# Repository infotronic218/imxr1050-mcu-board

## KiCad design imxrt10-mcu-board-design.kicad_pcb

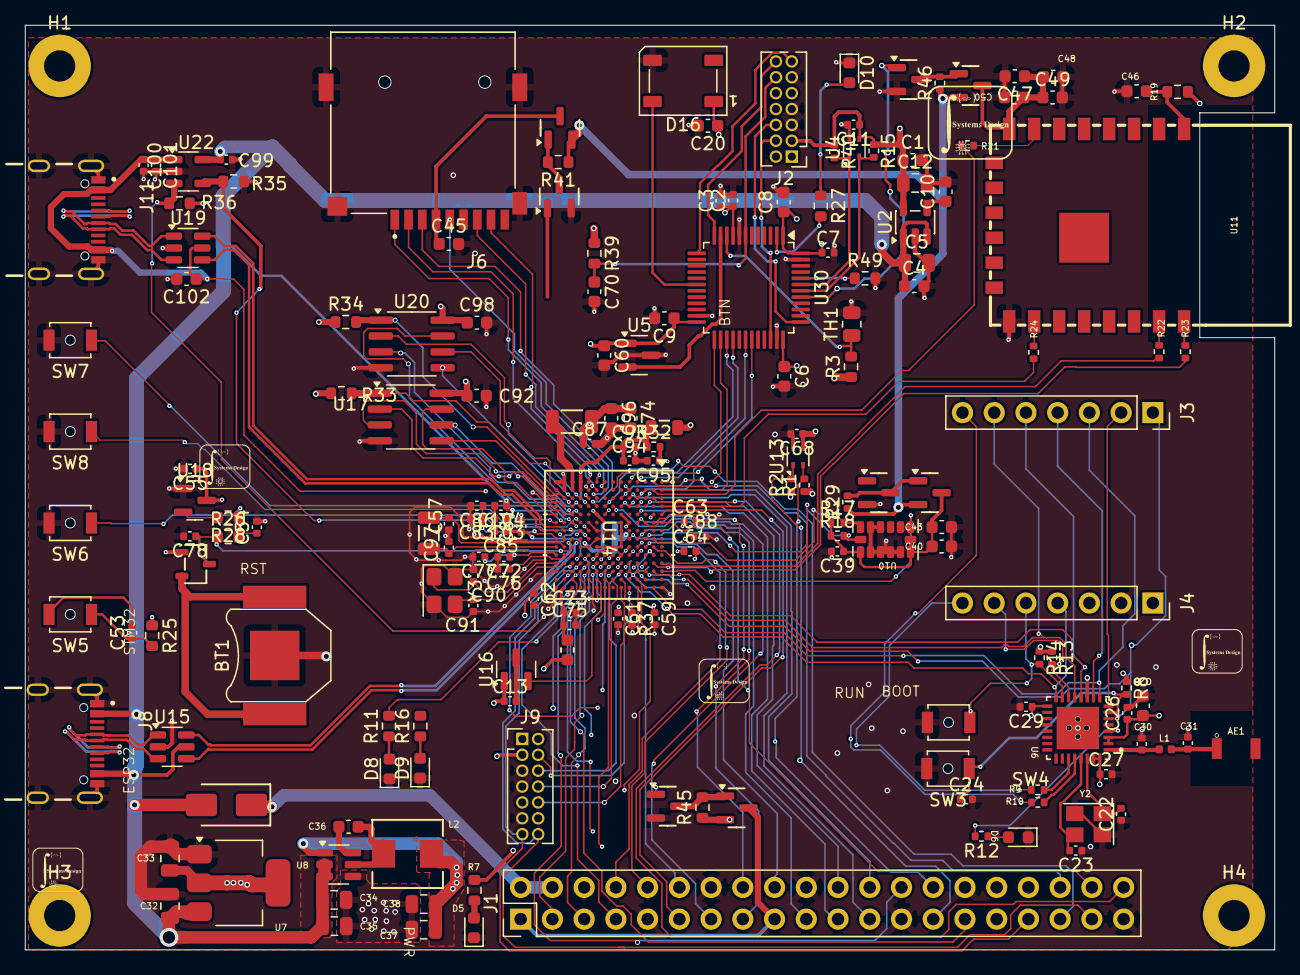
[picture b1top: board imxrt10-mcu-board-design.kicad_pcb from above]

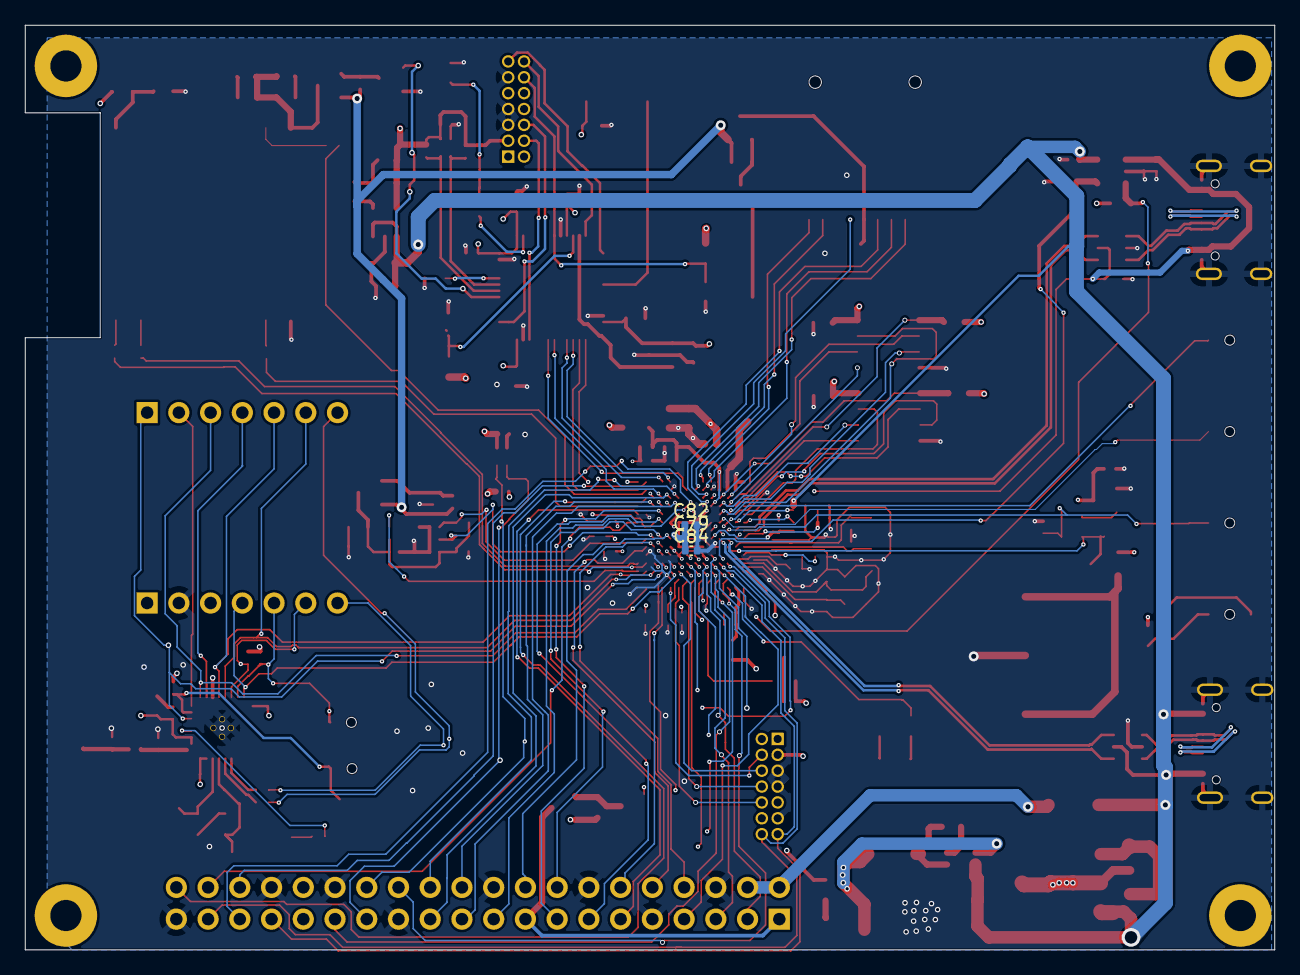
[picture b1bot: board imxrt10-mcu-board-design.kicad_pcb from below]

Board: 4 copper layers, 100.0 x 74.0 mm, 182 parts (3 on the bottom side), 158 nets.

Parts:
AE1: RFANT3216120A5T; FILTER-SMD_1206-2P-L3.2-W1.6-L
BT1: Battery_Cell; BatteryHolder_Keystone_2998_1x6.8mm
C1, C8, C9, C36, C40, C45, C46, C47, C60, C70, C92, C98: 100n; C_0603_1608Metric
C2, C3, C7, C73, C79, C93, C94, C99, C100: 2.2u; C_0402_1005Metric
C4, C10: 470n; C_0603_1608Metric
C5, C12: 10u; C_0805_2012Metric
C6, C28, C43, C48, C49, C50, C74, C96, C102: 10uF; C_0603_1608Metric
C11, C13, C24, C26, C27, C29, C53, C54, C55, C59, C61, C62, C63, C64, C68, C75, C82, C84, C87, C88, C101, C103, C104: 100n; C_0402_1005Metric
C20: 22u; C_0603_1608Metric
C22, C23, C57, C90, C91, C97: 10pF; C_0402_1005Metric
C30, C31: 1.5pF; C_0402_1005Metric
C32, C33, C34, C35, C37, C38: 22uF; C_0805_2012Metric
C39, C77, C85, C86: 10uF; C_0402_1005Metric
C72, C76, C78, C81, C83: 220n; C_0402_1005Metric
C95: 0.22u; C_0402_1005Metric
D5, D6, D8: LED, RED; LED_0603_1608Metric
D9: LED, White; LED_0603_1608Metric
D10: LED, Yellow; LED_0603_1608Metric
D12: BAV70-C68978; SOT-23-3_L3.0-W1.7-P0.95-LS2.9-BR
D13: SS34; D_SMA
D16: LED WS2812B; LED_WS2812B_PLCC4_5.0x5.0mm_P3.2mm
FB2: FB_0805
FB3: FB_0603
H1, H2, H3, H4: MountingHole_Pad; MountingHole_2.5mm_Pad
J1: Conn_02x20_Odd_Even; PinHeader_2x20_P2.54mm_Vertical
J2, J9: Conn_ST_STDC14; PinHeader_2x07_P1.27mm_Vertical
J3, J4: Conn_01x07; PinSocket_1x07_P2.54mm_Vertical
J6: MSD-4-A; CUI_MSD-4-A
J8, J11: USB4105-GF-A; GCT_USB4105-GF-A
L1: 2.4nH; L_0402_1005Metric
L2: 3.3uH; LMLP0506M3R3DTAS_AVX
L3: 4.7uH,25mA; L_1206
Q1, Q2, Q3, Q8: HL3401; Q_SOT-23
Q4, Q5, Q6, Q7: 2N7002K; Q_SOT-23
R1, R2, R8, R13, R14, R15, R17, R18, R29, R37, R40, R46: 10K; R_0402_1005Metric
R3, R19, R25, R33, R34, R35, R36, R39, R41, R45, R49: 10K; R_0603_1608Metric
R7, R11, R16, R27, R28: 750R; R_0603_1608Metric
R9: 0R; R_0402_1005Metric
R10: 470R; R_0402_1005Metric
R12: 750R; R_0402_1005Metric
R21, R22, R23, R24: 1K; R_0402_1005Metric
R26: 100K; R_0603_1608Metric
R32: 30K; R_0402_1005Metric
SW3, SW4, SW5, SW7, SW8: BOOT; SW_SPST_B3U-1000P-B
SW6: RST; SW_SPST_B3U-1000P-B
TH1: Thermistor_NTC 10k; R_0805_2012Metric
U2: SPX3819M5-L-3-3; SOT-23-5
U4, U13: SHT4x; Sensirion_DFN-4_1.5x1.5mm_P0.8mm_SHT4x_NoCentralPad
U5, U16: MCP9701T-E/TT; SOT-23
U6: ESP32-C3FH4
U7: AMS1117-3.3; SOT-223-3_TabPin2
U8: AP63203WU; TSOT-23-6
U10: ADXL343; LGA-14_3x5mm_P0.8mm_LayoutBorder1x6y
U11: WIZFI360-PA; WIFIM-SMD_WIZFI360-PA
U14: MIMXRT1052DVL6B; MAPBGA196_10X10_NXP
U15, U19: USBLC6-2SC6; SOT-23-6
U17: W25Q128JVS; SOIC-8_3.9x4.9mm_P1.27mm
U18: TPS3839DBZ; SOT-23
U20: APS1604M-3SQRx-SN; SOIC-8_3.9x4.9mm_P1.27mm
U22: TPS2051CDBV; SOT-23-5
U30: STM32F103C8Tx; LQFP-48_7x7mm_P0.5mm
X1: Q13FC1350000400; FC-135R_L3.2-W1.5
Y2, Y3: 40MHz, X252040MMB4SI; Crystal_SMD_3225-4Pin_3.2x2.5mm

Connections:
+3.3V: C13.1, C26.1, C27.1, C28.1, C29.1, C33.1, C55.1, C59.1, C61.1, C62.1, C63.1, C64.1, C68.1, C92.1, C98.1, D12.1, FB2.1, FB3.2, J9.3 (VCC), R1.1, R2.1, R7.2, R8.1, R13.1, R14.1, R19.1, R25.1, R33.1, R34.1, R36.1, U6.2 (VDD3P3), U6.3 (VDD3P3), U6.11 (VDD3P3_RTC), U6.17 (VDD3P3_CPU), U6.31 (VDDA), U6.32 (VDDA), U7.2 (VO), U13.3 (VDD), U14.E6 (NVCC_EMC), U14.E9 (NVCC_GPIO), U14.F5 (NVCC_EMC), U14.F10 (NVCC_GPIO), U14.J10 (NVCC_GPIO), U14.P12 (VDD_HIGH_IN), U16.1 (Vdd), U17.8 (VCC), U18.3 (VDD), U20.8 (VDD)
+3.3V1: C1.1, C2.1, C3.1, C6.1, C7.1, C8.1, C9.1, C11.1, C12.1, C20.1, C60.1, D16.1 (VDD), J2.3 (VCC), R3.1, R15.1, R39.1, R40.1, U2.5 (OUT), U4.3 (VDD), U5.1 (Vdd), U30.1 (VBAT), U30.9 (VDDA), U30.24 (VDD), U30.36 (VDD), U30.48 (VDD)
+3.3V_EXT: J1.1, J1.17, Q2.3 (D)
+3.3V_MPU: C39.1, C40.1, C43.1, Q8.3 (D), R17.1, R18.1, U10.1 (Vdd_I/O), U10.6 (Vs), U10.7 (~CS)
+3.3V_SD: C45.1, J6.4 (VDD), Q1.3 (D)
+3.3V_SYS: C37.1, C38.1, L2.2, Q1.2 (S), Q2.2 (S), Q3.2 (S), Q8.2 (S), R29.1, R41.1, R45.1, R46.1, U8.1 (FB)
+3.3V_WIFI: C47.1, C48.1, C49.1, C50.1, Q3.3 (D), U11.8 (VCC)
/EXT_IO0_I2C0_SCL: J1.28, R1.2, U13.2 (SCL), U14.J11 (GPIO_AD_B1_00)
/EXT_IO1_I2C0_SDA: J1.27, R2.2, U13.1 (SDA), U14.K11 (GPIO_AD_B1_01)
/EXT_IO2_I2C1_SDA: J1.3, U14.J12 (GPIO_AD_B1_06)
/EXT_IO3_I2C1_SCL: J1.5, U14.K10 (GPIO_AD_B1_07)
/EXT_IO4: J1.7, U14.L12 (GPIO_AD_B1_04)
/EXT_IO5: J1.29, U14.K12 (GPIO_AD_B1_05)
/EXT_IO6: J1.31, U14.H13 (GPIO_AD_B1_08)
/EXT_IO7: J1.26, U14.M13 (GPIO_AD_B1_09)
/EXT_IO8_SPI_CS: J1.24, U14.F3 (GPIO_EMC_01)
/EXT_IO9_SPI_MISO: J1.21, U14.F4 (GPIO_EMC_02)
/EXT_IO10_SPI_MOSI: J1.19, U14.G4 (GPIO_EMC_03)
/EXT_IO11_SPI_SCK: J1.23, U14.E3 (GPIO_EMC_00)
/EXT_IO12: J1.32, U14.L13 (GPIO_AD_B1_10)
/EXT_IO13_UART2_TX: J1.33, J9.13 (VCP_RX), U14.M12 (GPIO_AD_B1_03)
/EXT_IO14_UART1_RX: J1.8, U14.C9 (GPIO_B0_09)
/EXT_IO15_UART1_TX: J1.10, U14.B9 (GPIO_B0_08)
/EXT_IO16_UART1_RTS: J1.36, U14.B1 (GPIO_EMC_15)
/EXT_IO17_UART1_CTS: J1.11, U14.A5 (GPIO_EMC_16)
/EXT_IO18: J1.12, U14.D14 (GPIO_B1_13)
/EXT_IO19: J1.35, U14.H4 (GPIO_EMC_07)
/EXT_IO20: J1.38, U14.A6 (GPIO_EMC_13)
/EXT_IO21: J1.40, U14.B3 (GPIO_EMC_26)
/EXT_IO22: J1.15, U14.D5 (GPIO_EMC_32)
/EXT_IO23_CAN_TX: J1.16, U14.D8 (GPIO_B0_03)
/EXT_IO24_CAN_RX: J1.18, U14.E8 (GPIO_B0_02)
/EXT_IO25: J1.22, U14.C4 (GPIO_EMC_33)
/EXT_IO26_UART2_RX: J1.37, J9.14 (VCP_TX), U14.L11 (GPIO_AD_B1_02)
/EXT_IO27: J1.13, U14.D6 (GPIO_EMC_38)
/EXT_PWR_EN: Q6.1 (G), U14.D13 (GPIO_B1_12)
/MPU_INT: U10.8 (INT1), U14.A12 (GPIO_B1_08)
/USART3_CTS: R24.2, U14.A4 (GPIO_EMC_17)
/USART3_RTS: R21.2, U14.B2 (GPIO_EMC_18)
/USART3_RX: R23.2, U14.B11 (GPIO_B1_01)
/USART3_TX: R22.2, U14.A11 (GPIO_B1_00)
/WIZ_PWEN: Q5.1 (G), U30.41 (PB5)
/WIZ_RST: C46.1, R19.2, U11.1 (RST)
/esp32_wifi_section/ESP_RX: J4.7, R9.1, U14.M11 (GPIO_AD_B0_02)
/esp32_wifi_section/ESP_STATUS_LED: R12.2, U6.4 (XTAL_32K_P)
/esp32_wifi_section/ESP_TX: J3.7, R10.1, U14.G11 (GPIO_AD_B0_03)
/esp32_wifi_section/IO2_SPI_MISO: J3.1, U6.6 (GPIO2), U14.D12 (GPIO_B1_05)
/esp32_wifi_section/IO3_HS: J3.2, U6.8 (GPIO3)
/esp32_wifi_section/IO4_DATA_RDY: J3.3, U6.9 (MTMS), U14.B14 (GPIO_B1_15)
/esp32_wifi_section/IO5: J3.4, U6.10 (MTDI)
/esp32_wifi_section/IO6_SPI_CLK: J3.5, U6.12 (MTCK), U14.B12 (GPIO_B1_07)
/esp32_wifi_section/IO7_SPI_MOSI: J3.6, U6.13 (MTDO), U14.C12 (GPIO_B1_06)
/esp32_wifi_section/IO8: J4.6, R13.2, U6.14 (GPIO8)
/esp32_wifi_section/IO9: J4.5, R14.2, SW4.1, U6.15 (GPIO9)
/esp32_wifi_section/IO10_CS: J4.4, U6.16 (GPIO10), U14.E12 (GPIO_B1_04)
/esp32_wifi_section/LNA_IN: C30.1, L1.1, U6.1 (LNA_IN)
/esp32_wifi_section/RST: C24.1, R8.2, SW3.1, U6.7 (CHIP_EN)
/esp32_wifi_section/XTAL_N: C23.2, U6.29 (XTAL_N), Y2.3
/esp32_wifi_section/XTAL_P: C22.2, U6.30 (XTAL_P), Y2.1
/imxrt10-schematic/ADC_IN0: U14.J13 (GPIO_AD_B1_11), U16.2 (Vout)
/imxrt10-schematic/D2+: J11.A6 (DP1), J11.B6 (DP2), U19.3 (I/O2)
/imxrt10-schematic/D2-: J11.A7 (DN1), J11.B7 (DN2), U19.1 (I/O1)
/imxrt10-schematic/D+: J8.A6 (DP1), J8.B6 (DP2), U15.3 (I/O2)
/imxrt10-schematic/D-: J8.A7 (DN1), J8.B7 (DN2), U15.1 (I/O1)
/imxrt10-schematic/I2C2_SCL: R18.2, U10.14 (SCL/SCLK), U14.C8 (GPIO_B0_04)
/imxrt10-schematic/I2C2_SDA: R17.2, U10.13 (SDA/SDI/SDIO), U14.B8 (GPIO_B0_05)
/imxrt10-schematic/JTAG_MODE: R37.1, U14.F13 (GPIO_AD_B0_08)
/imxrt10-schematic/JTAG_SWDCLK: J9.6 (JCLK/SWCLK), U14.F12 (GPIO_AD_B0_07)
/imxrt10-schematic/JTAG_SWDIO: J9.4 (JTMS/SWDIO), U14.E14 (GPIO_AD_B0_06)
/imxrt10-schematic/JTAG_TDI: J9.10 (JTDI/NC), U14.F14 (GPIO_AD_B0_09)
/imxrt10-schematic/JTAG_TDO: J9.8 (JTDO/SWO), U14.G13 (GPIO_AD_B0_10)
/imxrt10-schematic/LED1: R11.2, U14.M14 (GPIO_AD_B0_00)
/imxrt10-schematic/POR_B: C54.1, R26.2, R28.1, SW6.1, U14.M7 (POR_B)
/imxrt10-schematic/SPI1_CS0: U14.C6 (GPIO_EMC_30), U30.25 (PB12)
/imxrt10-schematic/SPI1_SCK: U14.A2 (GPIO_EMC_27), U30.26 (PB13)
/imxrt10-schematic/SPI1_SDI: U14.E1 (GPIO_EMC_29), U30.27 (PB14)
/imxrt10-schematic/SPI1_SDO: U14.D1 (GPIO_EMC_28), U30.28 (PB15)
/imxrt10-schematic/UART5_RX: U14.D3 (GPIO_EMC_24), U30.30 (PA9)
/imxrt10-schematic/UART5_TX: U14.G2 (GPIO_EMC_23), U30.31 (PA10)
/imxrt10-schematic/USB_HOST_PWR_EN: R35.1, U14.L10 (GPIO_AD_B0_15), U22.4 (EN)
/imxrt10-schematic/USB_HOST_PWR_OC: R36.2, U14.H14 (GPIO_AD_B0_14), U22.3 (~FLT)
/imxrt10-schematic/USB_OTG_1_D+: U14.L8 (USB_OTG1_DP), U15.4 (I/O2)
/imxrt10-schematic/USB_OTG_1_D-: U14.M8 (USB_OTG1_DN), U15.6 (I/O1)
/imxrt10-schematic/USB_OTG_2_D+: U14.P7 (USB_OTG2_DP), U19.4 (I/O2)
/imxrt10-schematic/USB_OTG_2_D-: U14.N7 (USB_OTG2_DN), U19.6 (I/O1)
/imxrt10-schematic/USR_BTN: C53.1, R25.2, SW5.1
/imxrt10-schematic/VDD_SNVS_IN: C78.1, D12.3, R26.1, U14.M9 (VDD_SNVS_IN)
/imxrt10-schematic/XTAL_N: C91.2, U14.N11 (XTALO), Y3.3
/imxrt10-schematic/XTAL_P: C90.2, U14.P11 (XTALI), Y3.1
/stm32f103-mcu-interface/BOOT0: R49.1, U30.44 (BOOT0)
/stm32f103-mcu-interface/DIN: D16.4 (DIN), U30.18 (PB0)
/stm32f103-mcu-interface/I2C1_SCL: R15.2, U4.2 (SCL), U30.42 (PB6)
/stm32f103-mcu-interface/I2C1_SDA: R40.2, U4.1 (SDA), U30.43 (PB7)
/stm32f103-mcu-interface/LED3: R27.2, U30.2 (PC13)
/stm32f103-mcu-interface/NRST: C70.1, J2.12 (~RST), R39.2, U30.7 (NRST)
/stm32f103-mcu-interface/NTC_TEMP: R3.2, TH1.1, U30.10 (PA0)
/stm32f103-mcu-interface/SWCLK: J2.6 (JCLK/SWCLK), U30.37 (PA14)
/stm32f103-mcu-interface/SWDIO: J2.4 (JTMS/SWDIO), U30.34 (PA13)
/stm32f103-mcu-interface/TH_Sensor: U5.2 (Vout), U30.11 (PA1)
/stm32f103-mcu-interface/UART2_RX: J2.13 (VCP_RX), U30.13 (PA3)
/stm32f103-mcu-interface/UART2_TX: J2.14 (VCP_TX), U30.12 (PA2)
FLEXSPI_A_CLK: U14.L4 (GPIO_SD_B1_07), U17.6 (CLK)
FLEXSPI_A_SD0: U14.P3 (GPIO_SD_B1_08), U17.5 (DI(IO0))
FLEXSPI_A_SD1: U14.N4 (GPIO_SD_B1_09), U17.2 (DO(IO1))
FLEXSPI_A_SD2: U14.P4 (GPIO_SD_B1_10), U17.3 (IO2)
FLEXSPI_A_SD3: U14.P5 (GPIO_SD_B1_11), U17.7 (IO3)
FLEXSPI_A_SS: R33.2, U14.L3 (GPIO_SD_B1_06), U17.1 (~CS)
FLEXSPI_B_CLK: U14.P2 (GPIO_SD_B1_04), U20.6 (SCLK)
FLEXSPI_B_SD0: U14.M4 (GPIO_SD_B1_03), U20.5 (SI/SIO0)
FLEXSPI_B_SD1: U14.M3 (GPIO_SD_B1_02), U20.2 (SO/SIO1)
FLEXSPI_B_SD2: U14.M5 (GPIO_SD_B1_01), U20.3 (SIO2)
FLEXSPI_B_SD3: U14.L5 (GPIO_SD_B1_00), U20.7 (SIO3)
FLEXSPI_B_SS: R34.2, U14.N3 (GPIO_SD_B1_05), U20.1 (~CE)
GND: BT1.2 (-), C1.2, C2.2, C3.2, C4.2, C5.2, C6.2, C7.2, C8.2, C9.2, C10.2, C11.2, C12.2, C13.2, C20.2, C22.1, C23.1, C24.2, C26.2, C27.2, C28.2, C29.2, C30.2, C31.2, C32.2, C33.2, C34.2, C35.2, C37.2, C38.2, C39.2, C40.2, C43.2, C45.2, C46.2, C47.2, C48.2, C49.2, C50.2, C54.2, C55.2, C57.1, C59.2, C60.2, C61.2, C62.2, C63.2, C64.2, C68.2, C70.2, C72.2, C73.2, C74.2, C75.2, C76.2, C77.2, C78.2, C79.2, C81.2, C82.2, C83.2, C84.2, C85.2, C86.2, C87.2, C88.2, C90.1, C91.1, C92.2, C93.2, C94.2, C95.2, C96.2, C97.1, C98.2, C99.2, C100.2, C101.2, C102.2, C103.2, C104.2, D5.1 (K), D6.1 (K), D8.1 (K), D9.1 (K), D10.1 (K), D16.3 (VSS), J1.6, J1.9, J1.14, J1.20, J1.25, J1.30, J1.34, J1.39, J2.5 (GND), J2.7 (GND), J2.11 (GNDDetect), J4.2, J6.6 (VSS), J6.G1 (COVER_GND), J6.G2 (COVER_GND), J6.G3 (COVER_GND), J6.G4 (COVER_GND), J8.A1_B12 (GND), J8.B1_A12 (GND), J8.SH1 (SHELL_GND), J8.SH2 (SHELL_GND), J8.SH3 (SHELL_GND), J8.SH4 (SHELL_GND), J9.5 (GND), J9.7 (GND), J9.11 (GNDDetect), J11.A1_B12 (GND), J11.B1_A12 (GND), J11.SH1 (SHELL_GND), J11.SH2 (SHELL_GND), J11.SH3 (SHELL_GND), J11.SH4 (SHELL_GND), Q4.2 (S), Q5.2 (S), Q6.2 (S), Q7.2 (S), R35.2, R37.2, R49.2, SW3.2, SW4.2, SW6.2, SW7.2, SW8.2, TH1.2, U2.2 (GND), U4.4 (VSS), U5.3 (GND), U6.33 (GND), U7.1 (GND), U8.4 (GND), U10.2 (GND), U10.3 (RES), U10.4 (GND), U10.5 (GND), U10.11 (RES), U10.12 (SDO/ADDR), U11.15 (GND), U13.4 (VSS), U14.A1 (VSS), U14.A14 (VSS), U14.B5 (VSS), U14.B10 (VSS), U14.E2 (VSS), U14.E13 (VSS), U14.G7 (VSS), U14.G8 (VSS), U14.H7 (VSS), U14.H8 (VSS), U14.J7 (VSS), U14.J8 (VSS), U14.K2 (VSS), U14.K6 (TEST_MODE), U14.K9 (NGND_KEL0), U14.K13 (VSS), U14.L9 (VSS), U14.N1 (DCDC_GND), U14.N2 (DCDC_GND), U14.N5 (VSS), U14.N8 (VSS), U14.P1 (VSS), U14.P14 (VSS), U15.2 (GND), U16.3 (GND), U17.4 (GND), U18.1 (GND), U19.2 (GND), U20.4 (VSS), U22.2 (GND), U30.8 (VSSA), U30.23 (VSS), U30.35 (VSS), U30.47 (VSS), Y2.2, Y2.4, Y3.2, Y3.4
unnamed: AE1.1 (A), C31.1, L1.2
unnamed: C53.2, SW5.2
unnamed: D5.2 (A), R7.1
unnamed: D6.2 (A), R12.1
unnamed: D8.2 (A), R11.1
unnamed: D9.2 (A), R16.1
unnamed: D10.2 (A), R27.1
unnamed: D13.1, J1.2, J1.4
unnamed: L3.1, U14.M1 (DCDC_LP), U14.M2 (DCDC_LP)
unnamed: Q1.1 (G), Q4.3 (D), R41.2
unnamed: Q2.1 (G), Q6.3 (D), R45.2
unnamed: Q3.1 (G), Q5.3 (D), R46.2
unnamed: Q7.3 (D), Q8.1 (G), R29.2
unnamed: C10.1, U2.4 (BP)
unnamed: R9.2, U6.27 (U0RXD)
unnamed: R10.2, U6.28 (U0TXD)
unnamed: C36.1, U8.6 (BST)
unnamed: C36.2, L2.1, U8.5 (SW)
unnamed: R21.1, U11.7 (PB9/CTS1)
unnamed: R24.1, U11.16 (PB10/RTSI)
unnamed: R22.1, U11.21 (RXD1/IIC_SCL)
unnamed: R23.1, U11.22 (TXD1/IIC_SDA)
unnamed: SW7.1, U14.M6 (ONOFF)
unnamed: C57.2, U14.N9 (RTC_XTALI), X1.1
unnamed: C97.2, U14.P9 (RTC_XTALO), X1.2
unnamed: SW8.1, U14.L6 (WAKEUP)
unnamed: C72.1, C77.1, U14.P10 (NVCC_PLL)
unnamed: C73.1, C75.1, FB3.1, U14.N14 (VDDA_ADC_3P3)
unnamed: C83.1, C86.1, U14.P8 (VDD_HIGH_CAP)
unnamed: C76.1, U14.M10 (VDD_SNVS_CAP)
unnamed: C81.1, C85.1, U14.K8 (VDD_USB_CAP)
unnamed: C93.1, C94.1, FB2.2, R32.1, U14.K4 (DCDC_IN_Q), U14.L1 (DCDC_IN), U14.L2 (DCDC_IN)
unnamed: C95.1, R32.2, U14.K3 (DCDC_PSWITCH)
unnamed: R28.2, U18.2 (~RESET)
SD_CMD: J6.3 (CMD), U14.J4 (GPIO_SD_B0_00)
SD_D0: J6.7 (DAT0), U14.J1 (GPIO_SD_B0_02)
SD_D1: J6.8 (DAT1), U14.K1 (GPIO_SD_B0_03)
SD_D2: J6.1 (DAT2), U14.H2 (GPIO_SD_B0_04)
SD_D3: J6.2 (CD/DAT3), U14.J2 (GPIO_SD_B0_05)
SD_SCK: J6.5 (CLK), U14.J3 (GPIO_SD_B0_01)
VBAT: BT1.1 (+), D12.2
VBUS: C4.1, C5.1, C32.1, C34.1, C35.1, C99.1, C104.1, D13.2, J8.A4_B9 (VBUS), J8.B4_A9 (VBUS), U2.1 (IN), U2.3 (EN), U7.3 (VI), U8.2 (EN), U8.3 (IN), U14.N6 (USB_OTG1_VBUS), U15.5 (VBUS), U22.5 (IN)
VBUS_HOST: C100.1, C101.1, C102.1, C103.1, J11.A4_B9 (VBUS), J11.B4_A9 (VBUS), U14.P6 (USB_OTG2_VBUS), U19.5 (VBUS), U22.1 (OUT)
VDD_CORE: C74.1, C79.1, C82.1, C84.1, C87.1, C88.1, C96.1, L3.2, U14.F6 (VDD_SOC_IN), U14.F7 (VDD_SOC_IN), U14.F8 (VDD_SOC_IN), U14.F9 (VDD_SOC_IN), U14.G6 (VDD_SOC_IN), U14.G9 (VDD_SOC_IN), U14.H6 (VDD_SOC_IN), U14.H9 (VDD_SOC_IN), U14.J5 (DCDC_SENSE), U14.J9 (VDD_SOC_IN)

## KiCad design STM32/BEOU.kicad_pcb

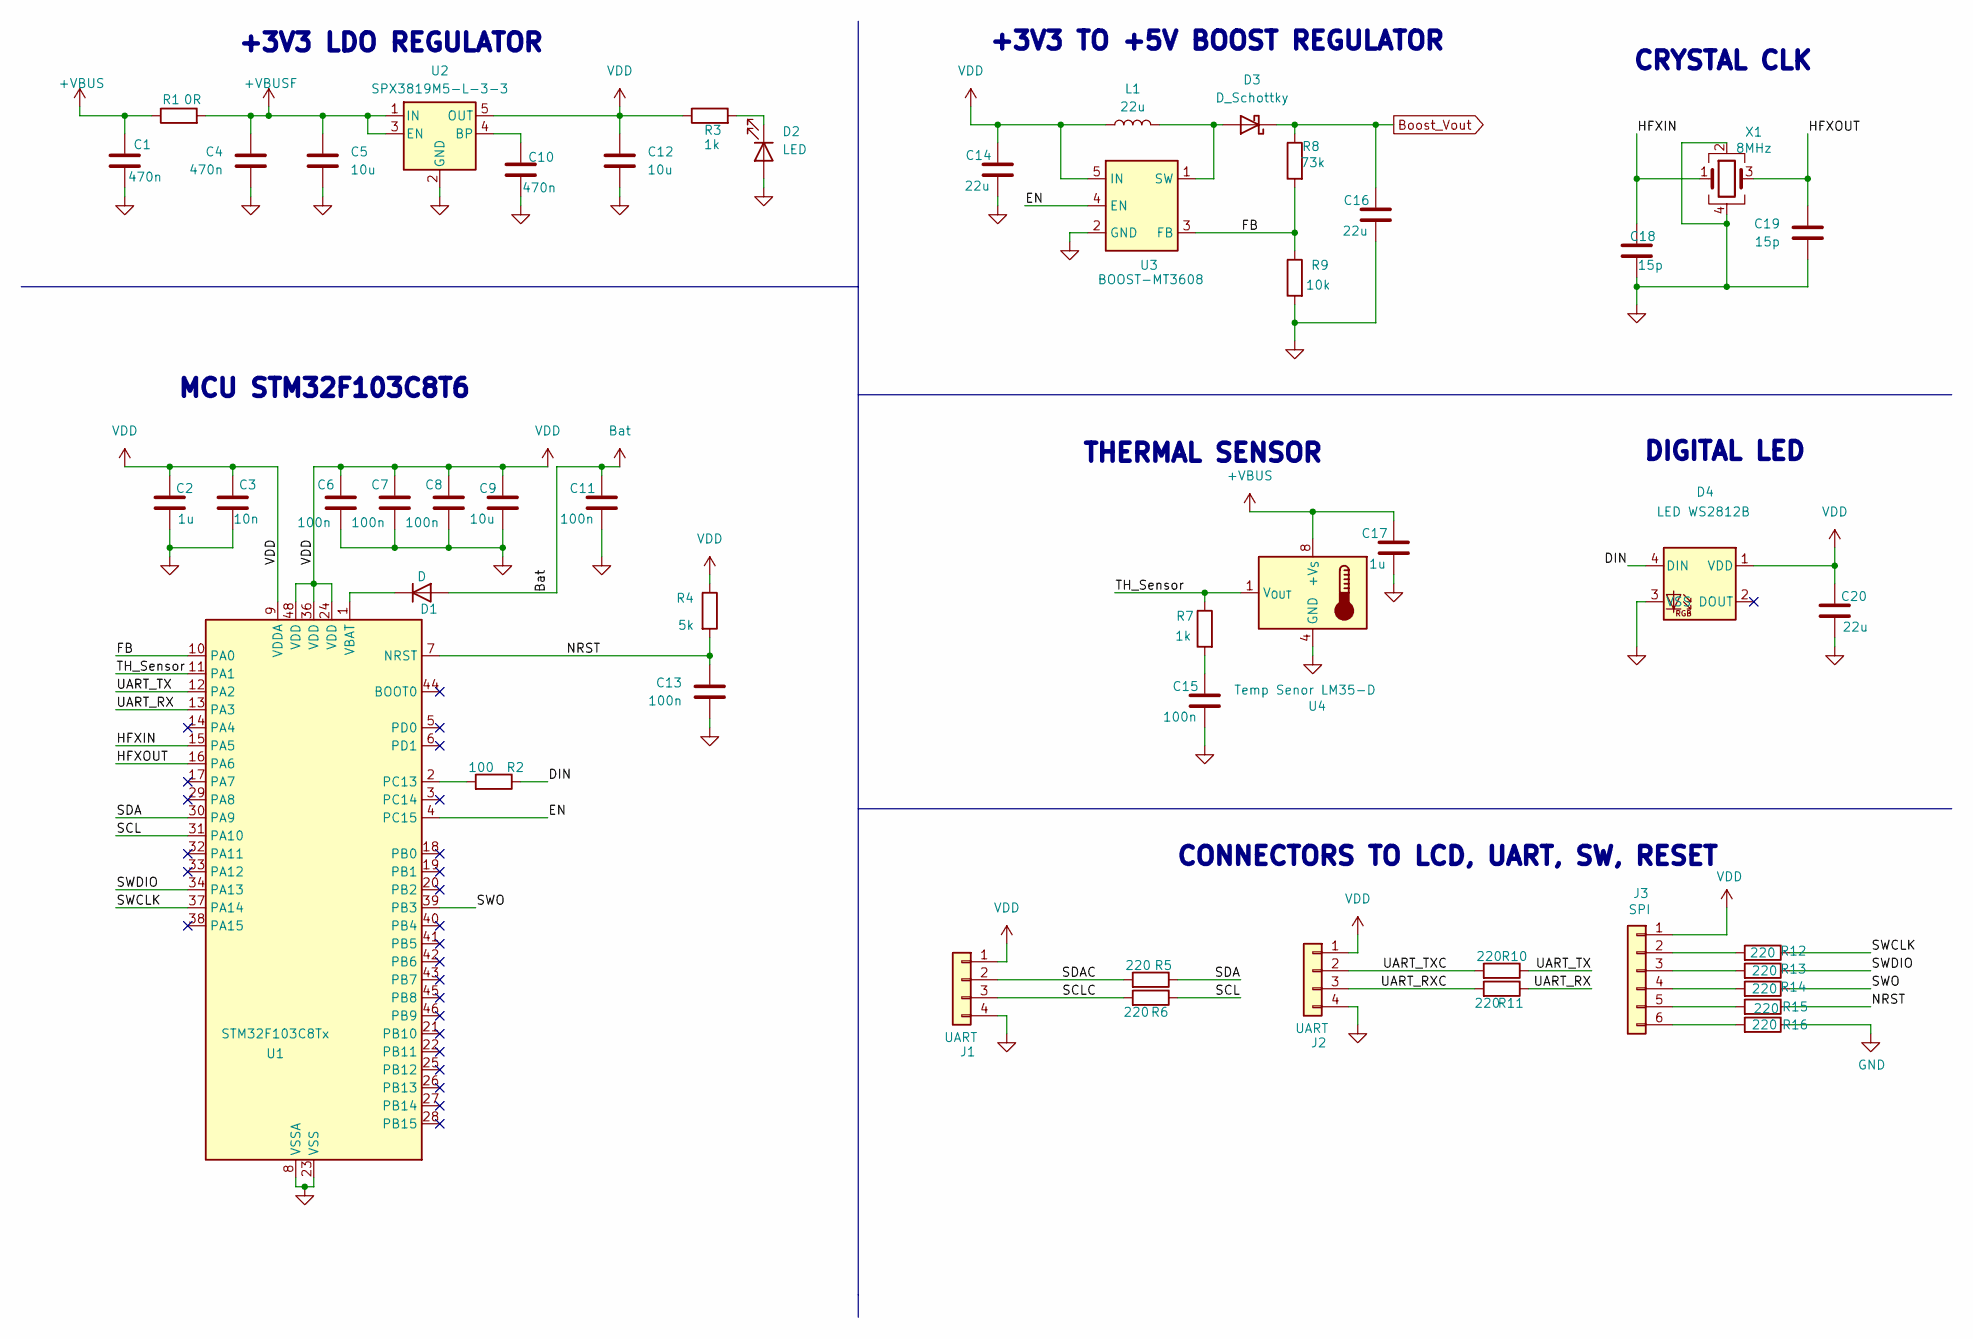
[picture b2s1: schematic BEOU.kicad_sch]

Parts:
C1, C4, C10: 470n; C_0603_1608Metric
C2, C17: 1u; C_0603_1608Metric
C3: 10n; C_0603_1608Metric
C5, C12: 10u; C_0805_2012Metric
C6, C7, C8, C11, C13, C15: 100n; C_0603_1608Metric
C9: 10u; C_0603_1608Metric
C14, C16, C20: 22u; C_0603_1608Metric
C18, C19: 15p; C_0603_1608Metric
D1: D; D_0201_0603Metric
D2: LED; LED_0603_1608Metric
D3: D_Schottky; D_0201_0603Metric
D4: LED WS2812B; LED_WS2812B_PLCC4_5.0x5.0mm_P3.2mm
J1, J2: UART; PinHeader_1x04_P2.54mm_Vertical
J3: SPI; JST_EH_B6B-EH-A_1x06_P2.50mm_Vertical
L1: 22u; L_0603_1608Metric
R1: 0R; R_0603_1608Metric
R2: 100; R_0201_0603Metric
R3: 1k; R_0603_1608Metric
R4: 5k; R_0603_1608Metric
R5, R6, R10, R11, R12, R13, R14, R15, R16: 220; R_0201_0603Metric
R7: 1k; R_0201_0603Metric
R8: 73k; R_0201_0603Metric
R9: 10k; R_0201_0603Metric
U1: STM32F103C8Tx; LQFP-48_7x7mm_P0.5mm
U2: SPX3819M5-L-3-3; SOT-23-5
U3: BOOST-MT3608; SOT-23-6
U4: Temp Senor LM35-D; SOIC-8_3.9x4.9mm_P1.27mm
X1: 8MHz; Crystal_SMD_3225-4Pin_3.2x2.5mm

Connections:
+VBUS: C1.1, C17.1, R1.1, U4.8 (+V_{S})
+VBUSF: C4.1, C5.1, R1.2, U2.1 (IN), U2.3 (EN)
/<NO NET>: C19.1, U1.16 (PA6), X1.3
/DIN: D4.4 (DIN), R2.1
/EN: U1.4 (PC15), U3.4 (EN)
/FB: R8.2, R9.1, U1.10 (PA0), U3.3 (FB)
/HFXIN: C18.1, U1.15 (PA5), X1.1
/NRST: C13.1, R4.2, R15.1, U1.7 (NRST)
/SCL: R6.1, U1.31 (PA10)
/SCLC: J1.3, R6.2
/SDA: R5.1, U1.30 (PA9)
/SDAC: J1.2, R5.2
/SWCLK: R12.1, U1.37 (PA14)
/SWDIO: R13.1, U1.34 (PA13)
/SWO: R14.1, U1.39 (PB3)
/TH_Sensor: R7.1, U1.11 (PA1), U4.1 (V_{OUT})
/UART_RX: R11.1, U1.13 (PA3)
/UART_RXC: J2.3, R11.2
/UART_TX: R10.1, U1.12 (PA2)
/UART_TXC: J2.2, R10.2
Bat: C11.1, D1.2 (A)
Boost_Vout: C16.1, D3.1 (K), R8.1
GND: C1.2, C2.2, C3.2, C4.2, C5.2, C6.2, C7.2, C8.2, C9.2, C10.2, C11.2, C12.2, C13.2, C14.2, C15.2, C16.2, C17.2, C18.2, C19.2, C20.2, D2.2 (A), D4.3 (VSS), J1.4, J2.4, R9.2, R16.1, U1.8 (VSSA), U1.23 (VSS), U1.35 (VSS), U1.47 (VSS), U2.2 (GND), U3.2 (GND), U4.4 (GND), X1.2, X1.4
unnamed: C15.1, R7.2
unnamed: D1.1 (K), U1.1 (VBAT)
unnamed: D2.1 (K), R3.2
unnamed: D3.2 (A), L1.2, U3.1 (SW)
unnamed: J3.2, R12.2
unnamed: J3.3, R13.2
unnamed: J3.4, R14.2
unnamed: J3.5, R15.2
unnamed: J3.6, R16.2
unnamed: R2.2, U1.2 (PC13)
unnamed: C10.1, U2.4 (BP)
VDD: C2.1, C3.1, C6.1, C7.1, C8.1, C9.1, C12.1, C14.1, C20.1, D4.1 (VDD), J1.1, J2.1, J3.1, L1.1, R3.1, R4.1, U1.9 (VDDA), U1.24 (VDD), U1.36 (VDD), U1.48 (VDD), U2.5 (OUT), U3.5 (IN)

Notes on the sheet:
DIGITAL LED
CRYSTAL CLK
THERMAL SENSOR
MCU STM32F103C8T6
+3V3 LDO REGULATOR
CONNECTORS TO LCD, UART, SW, RESET
+3V3 TO +5V BOOST REGULATOR

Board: 2 copper layers, 49 parts (0 on the bottom side), 35 nets, no tracks yet.

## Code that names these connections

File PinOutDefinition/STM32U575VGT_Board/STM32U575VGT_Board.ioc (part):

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Mcu.Name=STM32U575VGTx
Mcu.Package=LQFP100
Mcu.UserName=STM32U575VGTx
PA10.Signal=USART1_RX
PA11.Signal=USB_OTG_FS_DM
PA12.Signal=USB_OTG_FS_DP
PA2.Signal=USART2_TX
PA3.Signal=USART2_RX
PA4.Signal=OCTOSPIM_P1_NCS
PA6.Signal=OCTOSPIM_P1_IO3
PA7.Signal=OCTOSPIM_P1_IO2
PA9.Signal=USART1_TX
PB0.Signal=OCTOSPIM_P1_IO1
PB1.Signal=OCTOSPIM_P1_IO0
PB10.Signal=GPIO_Output
PB3\ (JTDO/TRACESWO).Signal=USART1_RTS
PB4\ (NJTRST).Signal=USART1_CTS
PB6.Signal=I2C1_SCL
PB7.Signal=I2C1_SDA
PB8.Signal=GPIO_Output
PB9.Signal=GPIO_Output
PC0.Signal=LPUART1_RX
PC1.Signal=LPUART1_TX
PC10.Signal=SDMMC1_D2
PC11.Signal=SDMMC1_D3
PC12.Signal=SDMMC1_CK
PC8.Signal=SDMMC1_D0
PC9.Signal=SDMMC1_D1
PD2.Signal=SDMMC1_CMD
PD8.Signal=USART3_TX
PD9.Signal=USART3_RX
PE10.Signal=OCTOSPIM_P1_CLK
PE12.Signal=SPI1_NSS
PE13.Signal=SPI1_SCK
PE14.Signal=SPI1_MISO
PE15.Signal=SPI1_MOSI
RCC.SYSCLKSource=RCC_SYSCLKSOURCE_PLLCLK
board=custom

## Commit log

2025-12-15 Initialize the project
2025-12-15 git push -u origin main
2025-12-15 Cleaning the project
2025-12-16 Update the source code
2025-12-17 Add files via upload
    stm32 part
2025-12-20 Update the schematic
2026-01-02 update the design
2026-01-03 Update the pcb routing
2026-01-03 Layout improvement
